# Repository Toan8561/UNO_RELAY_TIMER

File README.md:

#ARDUINO UNO SHIELD WITH POWER SUPPLY 5V

RELAY IS CONTROL WITH I2C PROTOCOL

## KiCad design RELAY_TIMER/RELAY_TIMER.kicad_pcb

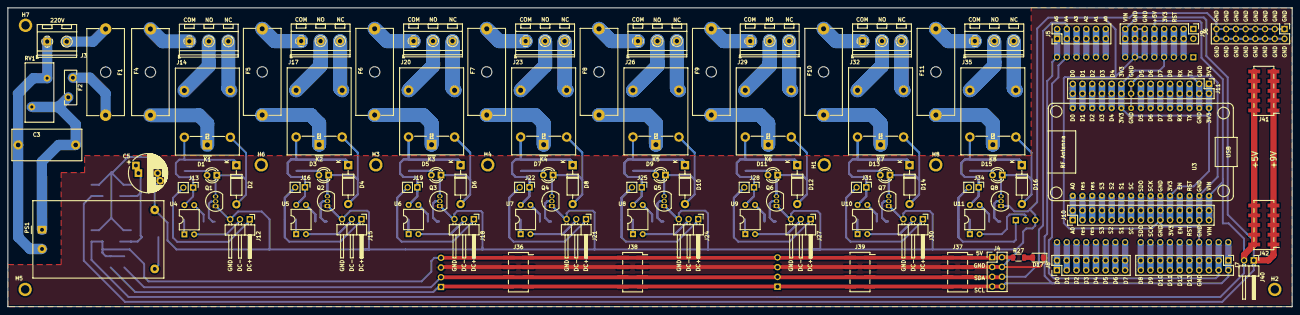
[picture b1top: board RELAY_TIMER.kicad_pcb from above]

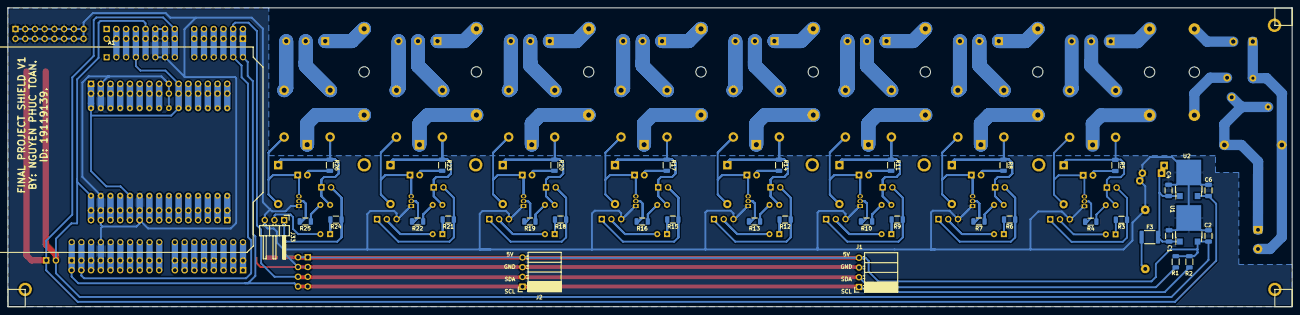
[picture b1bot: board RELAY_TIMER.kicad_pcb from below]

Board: 2 copper layers, 335.1 x 78.0 mm, 141 parts (37 on the bottom side), 152 nets.

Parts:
A1: Arduino_UNO_1_R3; Arduino_UNO_R3_SHIELD
C1, C4: 330nF; C_1206_3216Metric
C2, C6: 100nF; C_1206_3216Metric
C3: 0.1uF; C_Rect_L18.0mm_W8.0mm_P15.00mm_FKS3_FKP3
C5: 220uF; CP_Radial_D10.0mm_P5.00mm_P7.50mm
D1, D3, D5, D7, D9, D11, D13, D15: LED; LED_D3.0mm
D2, D4, D6, D8, D10, D12, D14, D16: 1N5819; D_DO-41_SOD81_P10.16mm_Horizontal
D17: LED; LED_1206_3216Metric
F1, F4, F5, F6, F7, F8, F9, F10, F11: SB_Fuse; Fuseholder_Cylinder-5x20mm_Schurter_0031_8201_Horizontal_Op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
F2: Fuse_(73dgr); Fuse_Bourns_MF-RHT300
F3: 13V 0.75A; Fuse_1812_4532Metric
H1, H2, H3, H4, H5, H6, H7, H8: MountingHole_Pad; MountingHole_2.2mm_M2_ISO7380_Pad
J1, J2: Conn_01x04_Female; PinSocket_1x04_P2.54mm_Horizontal
J3: Screw_Terminal_01x02; TerminalBlock_RND_205-00232_1x02_P5.08mm_Horizontal
J4: Conn_02x04_Odd_Even; PinHeader_2x04_P2.54mm_Vertical
J5: Conn_02x06_Odd_Even; PinHeader_2x06_P2.54mm_Vertical
J6, J8, J9: Conn_02x08_Odd_Even; PinHeader_2x08_P2.54mm_Vertical
J7: Conn_02x10_Odd_Even; PinHeader_2x10_P2.54mm_Vertical
J10, J11: Conn_02x15_Odd_Even; PinHeader_2x15_P2.54mm_Vertical
J12, J15, J18, J21, J24, J27, J30, J33: Conn_01x03; PinHeader_1x03_P2.54mm_Horizontal
J13, J16, J19, J22, J25, J28, J31, J34: Conn_01x02; PinHeader_1x02_P2.54mm_Vertical
J14, J17, J20, J23, J26, J29, J32, J35: Screw_Terminal_01x03; TerminalBlock_RND_205-00233_1x03_P5.08mm_Horizontal
J36, J37, J38, J39: Conn_02x04_Odd_Even; PinSocket_2x04_P2.54mm_Vertical_SMD
J40: Conn_01x02_Female; PinHeader_1x02_P2.54mm_Horizontal
J41, J42: Conn_02x05_Odd_Even; PinHeader_2x05_P2.54mm_Vertical_SMD
K1, K2, K3, K4, K5, K6, K7, K8: G5LE-1; Relay_SPDT_Omron-G5LE-1
PS1: HLK-5M12; Converter_ACDC_HiLink_HLK-PMxx
Q1, Q2, Q3, Q4, Q5, Q6, Q7, Q8: 2N3904; TO-92_Inline
R1, R2: 4.7K; R_1206_3216Metric
R3, R6, R9, R12, R15, R18, R21, R24: 100R; R_1206_3216Metric
R4, R7, R10, R13, R16, R19, R22, R25: 470R; R_1206_3216Metric
R5, R8, R11, R14, R17, R20, R23, R26, R27: 330R; R_1206_3216Metric
RV1: Varistor; RV_Disc_D15.5mm_W7.5mm_P7.5mm
U1: L7805; ATPAK-2
U2: L7809; ATPAK-2
U3: NodeMCU_ESP8266; NodeMCU1.0(12-E)_SHIELD
U4, U5, U6, U7, U8, U9, U10, U11: PC817; DIP-4_W7.62mm

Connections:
+5V: A1.5 (+5V), C2.1, J1.4, J2.4, J4.1, J4.2, J9.9, J9.10, J10.29, J10.30, J36.1, J36.2, J37.1, J37.2, J38.1, J38.2, J39.1, J39.2, J40.2, J41.2, J41.4, J41.6, J41.8, J41.10, J42.2, J42.4, J42.6, J42.8, J42.10, R1.1, R2.1, R27.1, U1.3 (OUT), U3.15 (+5V/Vin)
+9V: A1.8 (VIN), C6.1, J9.15, J9.16, J40.1, J41.1, J41.3, J41.5, J41.7, J41.9, J42.1, J42.3, J42.5, J42.7, J42.9, U2.3 (OUT)
+12V: C1.1, C4.1, C5.1, F3.2, U1.1 (IN), U2.1 (IN)
/3V3: A1.4 (3V3), J9.7, J9.8, J10.21, J10.22, J11.1, J11.2, J11.19, J11.20, U3.11 (3V3), U3.16 (3V3), U3.25 (3V3)
/30: A1.30 (AREF), J7.5, J7.6
/A0: A1.9 (A0), J5.11, J5.12
/A1: A1.10 (A1), J5.9, J5.10
/A2: A1.11 (A2), J5.7, J5.8
/A3: A1.12 (A3), J5.5, J5.6
/D0: A1.15 (D0/RX), J8.1, J8.2
/D1: A1.16 (D1/TX), J8.3, J8.4
/D2: A1.17 (D2), J8.5, J8.6
/D3: A1.18 (D3), J8.7, J8.8
/D4: A1.19 (D4), J8.9, J8.10
/D5: A1.20 (D5), J8.11, J8.12
/D6: A1.21 (D6), J8.13, J8.14
/D7: A1.22 (D7), J8.15, J8.16
/D8: A1.23 (D8), J7.19, J7.20
/D9: A1.24 (D9), J7.17, J7.18
/D10: A1.25 (D10), J7.15, J7.16
/D11: A1.26 (D11), J7.13, J7.14
/D12: A1.27 (D12), J7.11, J7.12
/D13: A1.28 (D13), J7.9, J7.10
/ESP1: J10.1, J10.2, U3.1 (A0)
/ESP2: J10.3, J10.4, U3.2 (res)
/ESP3: J10.5, J10.6, U3.3 (res)
/ESP4: J10.7, J10.8, U3.4 (SDD3/GPIO10)
/ESP5: J10.9, J10.10, U3.5 (SDD2/GPIO9)
/ESP6: J10.11, J10.12, U3.6 (SDD1/GPIO8/MOSI)
/ESP7: J10.13, J10.14, U3.7 (SDCMD/GPIO11/CS)
/ESP8: J10.15, J10.16, U3.8 (SDD0/GPIO7/MISO)
/ESP9: J10.17, J10.18, U3.9 (SCLK/GPIO6)
/ESP12: J10.23, J10.24, U3.12 (EN)
/ESP13: J10.25, J10.26, U3.13 (RST)
/ESP18: J11.5, J11.6, U3.18 (TXD0/GPIO1)
/ESP19: J11.7, J11.8, U3.19 (RXD0/GPIO3)
/ESP20: J11.9, J11.10, U3.20 (TXD2/CS/GPIO15/D8)
/ESP21: J11.11, J11.12, U3.21 (RXD2/MOSI/GPIO13/D7)
/ESP22: J11.13, J11.14, U3.22 (MISO/GPIO14/D6)
/ESP23: J11.15, J11.16, U3.23 (SCLK/GPIO14/D5)
/ESP26: J11.21, J11.22, U3.26 (TXD1/GPIO2/D4)
/ESP27: J11.23, J11.24, U3.27 (FLASH/GPIO0/D3)
/ESP28: J11.25, J11.26, U3.28 (SDA/GPIO4/D2)
/ESP29: J11.27, J11.28, U3.29 (SCL/GPIO5/D1)
/ESP30: J11.29, J11.30, U3.30 (WAKE/GPIO16/D0)
/IOREF: A1.2 (IOREF), J9.3, J9.4
/RST: A1.3 (~RESET), J9.5, J9.6
/Relay_Block_1/JD_VCC: D2.1 (K), J13.1, K1.5, R5.1, U4.4
/Relay_Block_2/JD_VCC: D4.1 (K), J16.1, K2.5, R8.1, U5.4
/Relay_Block_3/JD_VCC: D6.1 (K), J19.1, K3.5, R11.1, U6.4
/Relay_Block_4/JD_VCC: D8.1 (K), J22.1, K4.5, R14.1, U7.4
/Relay_Block_5/JD_VCC: D10.1 (K), J25.1, K5.5, R17.1, U8.4
/Relay_Block_6/JD_VCC: D12.1 (K), J28.1, K6.5, R20.1, U9.4
/Relay_Block_7/JD_VCC: D14.1 (K), J31.1, K7.5, R23.1, U10.4
/Relay_Block_8/JD_VCC: D16.1 (K), J34.1, K8.5, R26.1, U11.4
AC/L: F1.1, J3.2
AC/N: C3.2, J3.1, PS1.2 (AC/N), RV1.2
GND: A1.6 (GND), A1.7 (GND), A1.29 (GND), C1.2, C2.2, C4.2, C5.2, C6.2, D17.1 (K), J1.3, J2.3, J4.3, J4.4, J6.1, J6.2, J6.3, J6.4, J6.5, J6.6, J6.7, J6.8, J6.9, J6.10, J6.11, J6.12, J6.13, J6.14, J6.15, J6.16, J7.7, J7.8, J9.11, J9.12, J9.13, J9.14, J10.19, J10.20, J10.27, J10.28, J11.3, J11.4, J11.17, J11.18, J12.3, J15.3, J18.3, J21.3, J24.3, J27.3, J30.3, J33.3, J36.3, J36.4, J37.3, J37.4, J38.3, J38.4, J39.3, J39.4, PS1.3 (-Vout), Q1.1 (E), Q2.1 (E), Q3.1 (E), Q4.1 (E), Q5.1 (E), Q6.1 (E), Q7.1 (E), Q8.1 (E), U1.2 (GND), U2.2 (GND), U3.10 (GND), U3.14 (GND), U3.17 (GND), U3.24 (GND)
unnamed: C3.1, F2.2, PS1.1 (AC/L), RV1.1
unnamed: D1.1 (K), D2.2 (A), K1.2, Q1.3 (C)
unnamed: D1.2 (A), R5.2
unnamed: D3.1 (K), D4.2 (A), K2.2, Q2.3 (C)
unnamed: D3.2 (A), R8.2
unnamed: D5.1 (K), D6.2 (A), K3.2, Q3.3 (C)
unnamed: D5.2 (A), R11.2
unnamed: D7.1 (K), D8.2 (A), K4.2, Q4.3 (C)
unnamed: D7.2 (A), R14.2
unnamed: D9.2 (A), R17.2
unnamed: D9.1 (K), D10.2 (A), K5.2, Q5.3 (C)
unnamed: D11.1 (K), D12.2 (A), K6.2, Q6.3 (C)
unnamed: D11.2 (A), R20.2
unnamed: D13.1 (K), D14.2 (A), K7.2, Q7.3 (C)
unnamed: D13.2 (A), R23.2
unnamed: D15.1 (K), D16.2 (A), K8.2, Q8.3 (C)
unnamed: D15.2 (A), R26.2
unnamed: D17.2 (A), R27.2
unnamed: F1.2, F2.1
unnamed: F3.1, PS1.4 (+Vout)
unnamed: F4.1, K1.1
unnamed: F4.2, J14.1
unnamed: F5.1, K2.1
unnamed: F5.2, J17.1
unnamed: F6.1, K3.1
unnamed: F6.2, J20.1
unnamed: F7.1, K4.1
unnamed: F7.2, J23.1
unnamed: F8.1, K5.1
unnamed: F8.2, J26.1
unnamed: F9.1, K6.1
unnamed: F9.2, J29.1
unnamed: F10.1, K7.1
unnamed: F10.2, J32.1
unnamed: F11.1, K8.1
unnamed: F11.2, J35.1
unnamed: J14.2, K1.4
unnamed: J14.3, K1.3
unnamed: J17.2, K2.4
unnamed: J17.3, K2.3
unnamed: J20.2, K3.4
unnamed: J20.3, K3.3
unnamed: J23.2, K4.4
unnamed: J23.3, K4.3
unnamed: J26.2, K5.4
unnamed: J26.3, K5.3
unnamed: J29.2, K6.4
unnamed: J29.3, K6.3
unnamed: J32.2, K7.4
unnamed: J32.3, K7.3
unnamed: J35.2, K8.4
unnamed: J35.3, K8.3
unnamed: Q1.2 (B), R4.2
unnamed: Q2.2 (B), R7.2
unnamed: Q3.2 (B), R10.2
unnamed: Q4.2 (B), R13.2
unnamed: Q5.2 (B), R16.2
unnamed: Q6.2 (B), R19.2
unnamed: Q7.2 (B), R22.2
unnamed: Q8.2 (B), R25.2
unnamed: R3.2, U4.1
unnamed: R4.1, U4.3
unnamed: R6.2, U5.1
unnamed: R7.1, U5.3
unnamed: R9.2, U6.1
unnamed: R10.1, U6.3
unnamed: R12.2, U7.1
unnamed: R13.1, U7.3
unnamed: R15.2, U8.1
unnamed: R16.1, U8.3
unnamed: R18.2, U9.1
unnamed: R19.1, U9.3
unnamed: R21.2, U10.1
unnamed: R22.1, U10.3
unnamed: R24.2, U11.1
unnamed: R25.1, U11.3
R1_DC+: J12.1, J13.2, R3.1
R1_DC-: J12.2, U4.2
R2_DC+: J15.1, J16.2, R6.1
R2_DC-: J15.2, U5.2
R3_DC+: J18.1, J19.2, R9.1
R3_DC-: J18.2, U6.2
R4_DC+: J21.1, J22.2, R12.1
R4_DC-: J21.2, U7.2
R5_DC+: J24.1, J25.2, R15.1
R5_DC-: J24.2, U8.2
R6_DC+: J27.1, J28.2, R18.1
R6_DC-: J27.2, U9.2
R7_DC+: J30.1, J31.2, R21.1
R7_DC-: J30.2, U10.2
R8_DC+: J33.1, J34.2, R24.1
R8_DC-: J33.2, U11.2
SCL: A1.14 (SCL/A5), A1.32 (SCL/A5), J1.1, J2.1, J4.7, J4.8, J5.1, J5.2, J7.1, J7.2, J36.7, J36.8, J37.7, J37.8, J38.7, J38.8, J39.7, J39.8, R2.2
SDA: A1.13 (SDA/A4), A1.31 (SDA/A4), J1.2, J2.2, J4.5, J4.6, J5.3, J5.4, J7.3, J7.4, J36.5, J36.6, J37.5, J37.6, J38.5, J38.6, J39.5, J39.6, R1.2

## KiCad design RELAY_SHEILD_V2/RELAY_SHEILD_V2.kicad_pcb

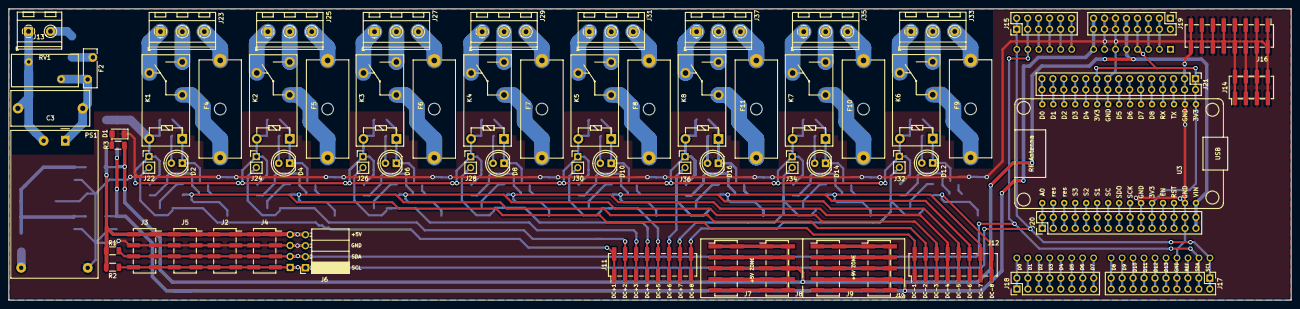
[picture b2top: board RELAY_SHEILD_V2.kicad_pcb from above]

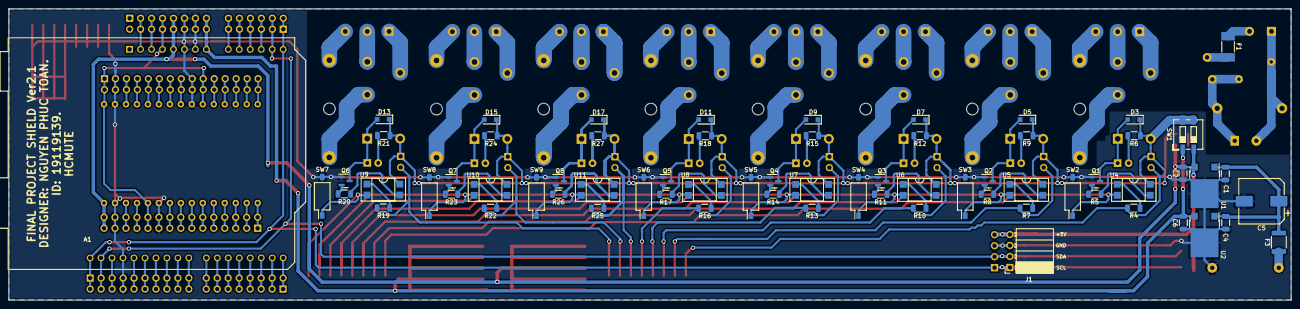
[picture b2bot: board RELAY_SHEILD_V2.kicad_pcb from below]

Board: 2 copper layers, 296.8 x 67.4 mm, 137 parts (68 on the bottom side), 145 nets.

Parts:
A1: Arduino_UNO_1_R3; Arduino_UNO_R3_SHIELD
C1, C4: 330nF; C_1206_3216Metric
C2, C6: 100nF; C_1206_3216Metric
C3: 0.1uF; C_Rect_L18.0mm_W8.0mm_P15.00mm_FKS3_FKP3
C5: 220uF; CP_Elec_10x10
D1: LED; LED_1206_3216Metric
D2, D4, D6, D8, D10, D12, D14, D16: LED; LED_D5.0mm
D3, D5, D7, D9, D11, D13, D15, D17: 1N5819; D_SOD-123F
F1: SB_Fuse; Fuse_Littelfuse-NANO2-451_453
F2: Fuse_(73dgr); Fuse_Bourns_MF-RHT300
F3: 13V 0.75A; Fuse_1812_4532Metric
F4, F5, F6, F7, F8, F9, F10, F11: SB_Fuse; Fuseholder_Cylinder-5x20mm_Schurter_0031_8201_Horizontal_Op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
J1, J6: Conn_1x4_F; PinSocket_1x04_P2.54mm_Horizontal
J2, J3, J4, J5: Conn_2x4; PinSocket_2x04_P2.54mm_Vertical_SMD
J7, J8, J9, J10: Conn_02x05_Odd_Even; PinHeader_2x05_P2.54mm_Vertical_SMD
J11, J12: Conn_02x16_Odd_Even; PinHeader_2x08_P2.54mm_Vertical_SMD
J13: Screw_Terminal_01x02; TerminalBlock_RND_205-00232_1x02_P5.08mm_Horizontal
J14: Conn_2x4; PinHeader_2x04_P2.54mm_Vertical_SMD
J15: Conn_02x06_Odd_Even; PinHeader_2x06_P2.54mm_Vertical
J16: Conn_02x08_Odd_Even; PinHeader_2x08_P2.54mm_Vertical_SMD
J17: Conn_02x10_Odd_Even; PinHeader_2x10_P2.54mm_Vertical
J18, J19: Conn_02x08_Odd_Even; PinHeader_2x08_P2.54mm_Vertical
J20, J21: Conn_02x15_Odd_Even; PinHeader_2x15_P2.54mm_Vertical
J22, J24, J26, J28, J30, J32, J34, J36: Conn_01x02; PinHeader_1x02_P2.54mm_Vertical
J23, J25, J27, J29, J31, J33, J35, J37: Screw_Terminal_01x03; TerminalBlock_RND_205-00233_1x03_P5.08mm_Horizontal
K1, K2, K3, K4, K5, K6, K7, K8: G5Q-1; Relay_SPDT_Omron-G5Q-1
PS1: HLK-5M12; Converter_ACDC_HiLink_HLK-PMxx
Q1, Q2, Q3, Q4, Q5, Q6, Q7, Q8: 2N3904; SOT-23
R1, R2: 4.7K; R_1206_3216Metric
R3, R6, R9, R12, R15, R18, R21, R24, R27: 330R; R_1206_3216Metric
R4, R7, R10, R13, R16, R19, R22, R25: 100R; R_1206_3216Metric
R5, R8, R11, R14, R17, R20, R23, R26: 470R; R_1206_3216Metric
RV1: Varistor; RV_Disc_D15.5mm_W7.5mm_P7.5mm
SW1: SW_DIP_x02; SW_DIP_SPSTx02_Slide_6.7x6.64mm_W6.73mm_P2.54mm_LowProfile_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
SW2, SW3, SW4, SW5, SW6, SW7, SW8, SW9: SW_DIP_x01; SW_DIP_SPSTx01_Slide_Omron_A6S-110x_W8.9mm_P2.54mm
U1: L7805; ATPAK-2
U2: L7809; ATPAK-2
U3: NodeMCU_ESP8266; NodeMCU1.0(12-E)_SHIELD
U4, U5, U6, U7, U8, U9, U10, U11: PC817; DIP-4_W7.62mm_SMDSocket_SmallPads

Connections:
+5V: A1.5 (+5V), C2.1, J1.4, J2.1, J2.2, J3.1, J3.2, J4.1, J4.2, J5.1, J5.2, J6.4, J7.1, J7.2, J7.3, J7.4, J7.5, J7.6, J7.7, J7.8, J7.9, J7.10, J8.1, J8.2, J8.3, J8.4, J8.5, J8.6, J8.7, J8.8, J8.9, J8.10, J19.9, J19.10, J20.29, J20.30, R1.1, R2.1, R3.1, SW1.2, U1.3 (OUT), U3.15 (+5V/Vin)
+9V: A1.8 (VIN), C6.1, J9.1, J9.2, J9.3, J9.4, J9.5, J9.6, J9.7, J9.8, J9.9, J9.10, J10.1, J10.2, J10.3, J10.4, J10.5, J10.6, J10.7, J10.8, J10.9, J10.10, J19.15, J19.16, SW1.1, U2.3 (OUT)
+12V: C1.1, C4.1, C5.1, F3.2, U1.1 (IN), U2.1 (IN)
/3V3: A1.4 (3V3), J19.7, J19.8, J20.21, J20.22, J21.1, J21.2, J21.19, J21.20, U3.11 (3V3), U3.16 (3V3), U3.25 (3V3)
/30: A1.30 (AREF), J17.5, J17.6
/A0: A1.9 (A0), J15.11, J15.12
/A1: A1.10 (A1), J15.9, J15.10
/A2: A1.11 (A2), J15.7, J15.8
/A3: A1.12 (A3), J15.5, J15.6
/D0: A1.15 (D0/RX), J18.1, J18.2
/D1: A1.16 (D1/TX), J18.3, J18.4
/D2: A1.17 (D2), J18.5, J18.6
/D3: A1.18 (D3), J18.7, J18.8
/D4: A1.19 (D4), J18.9, J18.10
/D5: A1.20 (D5), J18.11, J18.12
/D6: A1.21 (D6), J18.13, J18.14
/D7: A1.22 (D7), J18.15, J18.16
/D8: A1.23 (D8), J17.19, J17.20
/D9: A1.24 (D9), J17.17, J17.18
/D10: A1.25 (D10), J17.15, J17.16
/D11: A1.26 (D11), J17.13, J17.14
/D12: A1.27 (D12), J17.11, J17.12
/D13: A1.28 (D13), J17.9, J17.10
/ESP1: J20.1, J20.2, U3.1 (A0)
/ESP2: J20.3, J20.4, U3.2 (res)
/ESP3: J20.5, J20.6, U3.3 (res)
/ESP4: J20.7, J20.8, U3.4 (SDD3/GPIO10)
/ESP5: J20.9, J20.10, U3.5 (SDD2/GPIO9)
/ESP6: J20.11, J20.12, U3.6 (SDD1/GPIO8/MOSI)
/ESP7: J20.13, J20.14, U3.7 (SDCMD/GPIO11/CS)
/ESP8: J20.15, J20.16, U3.8 (SDD0/GPIO7/MISO)
/ESP9: J20.17, J20.18, U3.9 (SCLK/GPIO6)
/ESP12: J20.23, J20.24, U3.12 (EN)
/ESP13: J20.25, J20.26, U3.13 (RST)
/ESP18: J21.5, J21.6, U3.18 (TXD0/GPIO1)
/ESP19: J21.7, J21.8, U3.19 (RXD0/GPIO3)
/ESP20: J21.9, J21.10, U3.20 (TXD2/CS/GPIO15/D8)
/ESP21: J21.11, J21.12, U3.21 (RXD2/MOSI/GPIO13/D7)
/ESP22: J21.13, J21.14, U3.22 (MISO/GPIO14/D6)
/ESP23: J21.15, J21.16, U3.23 (SCLK/GPIO14/D5)
/ESP26: J21.21, J21.22, U3.26 (TXD1/GPIO2/D4)
/ESP27: J21.23, J21.24, U3.27 (FLASH/GPIO0/D3)
/ESP28: J21.25, J21.26, U3.28 (SDA/GPIO4/D2)
/ESP29: J21.27, J21.28, U3.29 (SCL/GPIO5/D1)
/ESP30: J21.29, J21.30, U3.30 (WAKE/GPIO16/D0)
/IOREF: A1.2 (IOREF), J19.3, J19.4
/RELAY_POWER: D3.1 (K), D5.1 (K), D7.1 (K), D9.1 (K), D11.1 (K), D13.1 (K), D15.1 (K), D17.1 (K), J22.1, J24.1, J26.1, J28.1, J30.1, J32.1, J34.1, J36.1, K1.5, K2.5, K3.5, K4.5, K5.5, K6.5, K7.5, K8.5, R6.1, R9.1, R12.1, R15.1, R18.1, R21.1, R24.1, R27.1, SW1.3, SW1.4, U4.4, U5.4, U6.4, U7.4, U8.4, U9.4, U10.4, U11.4
/RST: A1.3 (~RESET), J19.5, J19.6
DC+ _1: J11.1, J11.2, J22.2, R4.1
DC+ _2: J11.3, J11.4, J24.2, R7.1
DC+ _3: J11.5, J11.6, J26.2, R10.1
DC+ _4: J11.7, J11.8, J28.2, R13.1
DC+ _5: J11.9, J11.10, J30.2, R16.1
DC+ _6: J11.11, J11.12, J36.2, R25.1
DC+ _7: J11.13, J11.14, J34.2, R22.1
DC+ _8: J11.15, J11.16, J32.2, R19.1
DC- _1: J12.1, J12.2, SW2.1, U4.2
DC- _2: J12.3, J12.4, SW3.1, U5.2
DC- _3: J12.5, J12.6, SW4.1, U6.2
DC- _4: J12.7, J12.8, SW5.1, U7.2
DC- _5: J12.9, J12.10, SW6.1, U8.2
DC- _6: J12.11, J12.12, SW9.1, U11.2
DC- _7: J12.13, J12.14, SW8.1, U10.2
DC- _8: J12.15, J12.16, SW7.1, U9.2
GND: A1.6 (GND), A1.7 (GND), A1.29 (GND), C1.2, C2.2, C4.2, C5.2, C6.2, D1.1 (K), J1.3, J2.3, J2.4, J3.3, J3.4, J4.3, J4.4, J5.3, J5.4, J6.3, J14.1, J14.2, J14.3, J14.4, J14.5, J14.6, J14.7, J14.8, J16.1, J16.2, J16.3, J16.4, J16.5, J16.6, J16.7, J16.8, J16.9, J16.10, J16.11, J16.12, J16.13, J16.14, J16.15, J16.16, J17.7, J17.8, J19.11, J19.12, J19.13, J19.14, J20.19, J20.20, J20.27, J20.28, J21.3, J21.4, J21.17, J21.18, PS1.3 (-Vout), Q1.1 (E), Q2.1 (E), Q3.1 (E), Q4.1 (E), Q5.1 (E), Q6.1 (E), Q7.1 (E), Q8.1 (E), SW2.2, SW3.2, SW4.2, SW5.2, SW6.2, SW7.2, SW8.2, SW9.2, U1.2 (GND), U2.2 (GND), U3.10 (GND), U3.14 (GND), U3.17 (GND), U3.24 (GND)
unnamed: C3.1, F2.2, PS1.1 (AC/L), RV1.1
unnamed: C3.2, J13.1, PS1.2 (AC/N), RV1.2
unnamed: D1.2 (A), R3.2
unnamed: D2.1 (K), D3.2 (A), K1.1, Q1.3 (C)
unnamed: D2.2 (A), R6.2
unnamed: D4.1 (K), D5.2 (A), K2.1, Q2.3 (C)
unnamed: D4.2 (A), R9.2
unnamed: D6.1 (K), D7.2 (A), K3.1, Q3.3 (C)
unnamed: D6.2 (A), R12.2
unnamed: D8.1 (K), D9.2 (A), K4.1, Q4.3 (C)
unnamed: D8.2 (A), R15.2
unnamed: D10.1 (K), D11.2 (A), K5.1, Q5.3 (C)
unnamed: D10.2 (A), R18.2
unnamed: D12.1 (K), D13.2 (A), K6.1, Q6.3 (C)
unnamed: D12.2 (A), R21.2
unnamed: D14.1 (K), D15.2 (A), K7.1, Q7.3 (C)
unnamed: D14.2 (A), R24.2
unnamed: D16.1 (K), D17.2 (A), K8.1, Q8.3 (C)
unnamed: D16.2 (A), R27.2
unnamed: F1.1, J13.2
unnamed: F1.2, F2.1
unnamed: F3.1, PS1.4 (+Vout)
unnamed: F4.1, K1.2
unnamed: F4.2, J23.3
unnamed: F5.1, K2.2
unnamed: F5.2, J25.3
unnamed: F6.1, K3.2
unnamed: F6.2, J27.3
unnamed: F7.1, K4.2
unnamed: F7.2, J29.3
unnamed: F8.1, K5.2
unnamed: F8.2, J31.3
unnamed: F9.1, K6.2
unnamed: F9.2, J33.3
unnamed: F10.1, K7.2
unnamed: F10.2, J35.3
unnamed: F11.1, K8.2
unnamed: F11.2, J37.3
unnamed: J23.1, K1.4
unnamed: J23.2, K1.3
unnamed: J25.1, K2.4
unnamed: J25.2, K2.3
unnamed: J27.1, K3.4
unnamed: J27.2, K3.3
unnamed: J29.1, K4.4
unnamed: J29.2, K4.3
unnamed: J31.1, K5.4
unnamed: J31.2, K5.3
unnamed: J33.1, K6.4
unnamed: J33.2, K6.3
unnamed: J35.1, K7.4
unnamed: J35.2, K7.3
unnamed: J37.1, K8.4
unnamed: J37.2, K8.3
unnamed: Q1.2 (B), R5.2
unnamed: Q2.2 (B), R8.2
unnamed: Q3.2 (B), R11.2
unnamed: Q4.2 (B), R14.2
unnamed: Q5.2 (B), R17.2
unnamed: Q6.2 (B), R20.2
unnamed: Q7.2 (B), R23.2
unnamed: Q8.2 (B), R26.2
unnamed: R4.2, U4.1
unnamed: R5.1, U4.3
unnamed: R7.2, U5.1
unnamed: R8.1, U5.3
unnamed: R10.2, U6.1
unnamed: R11.1, U6.3
unnamed: R13.2, U7.1
unnamed: R14.1, U7.3
unnamed: R16.2, U8.1
unnamed: R17.1, U8.3
unnamed: R19.2, U9.1
unnamed: R20.1, U9.3
unnamed: R22.2, U10.1
unnamed: R23.1, U10.3
unnamed: R25.2, U11.1
unnamed: R26.1, U11.3
SCL: A1.14 (SCL/A5), A1.32 (SCL/A5), J1.1, J2.7, J2.8, J3.7, J3.8, J4.7, J4.8, J5.7, J5.8, J6.1, J15.1, J15.2, J17.1, J17.2, R2.2
SDA: A1.13 (SDA/A4), A1.31 (SDA/A4), J1.2, J2.5, J2.6, J3.5, J3.6, J4.5, J4.6, J5.5, J5.6, J6.2, J15.3, J15.4, J17.3, J17.4, R1.2

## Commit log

2023-05-26 add pcb design
2023-05-26 change time run
2023-05-28 Level 1 menu
2023-05-29 Level 2 menu
2023-05-30 Level 3 menu with ID for control
2023-05-31 Add relays support
2023-05-31 Add relays timer
2023-05-31 relays timer with menu
2023-05-31 fix some bug
2023-06-01 clean up the code
2023-06-01 new branch
2023-06-01 make some change
2023-06-01 change menu memory consumsion
2023-06-08 get ram down tho 75 percents
2023-06-08 do some clean up
2023-06-08 move pcb design
2023-06-08 Branching
2023-06-08 Menu change
